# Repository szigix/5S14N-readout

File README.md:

# 5S14N-readout
KiCAD design files for the readout board for the Tektronix 5S14N sampler plugin.

For Desxription see my blog entry at https://diysquared.blogspot.com/2021/03/readout-for-5s14n.html

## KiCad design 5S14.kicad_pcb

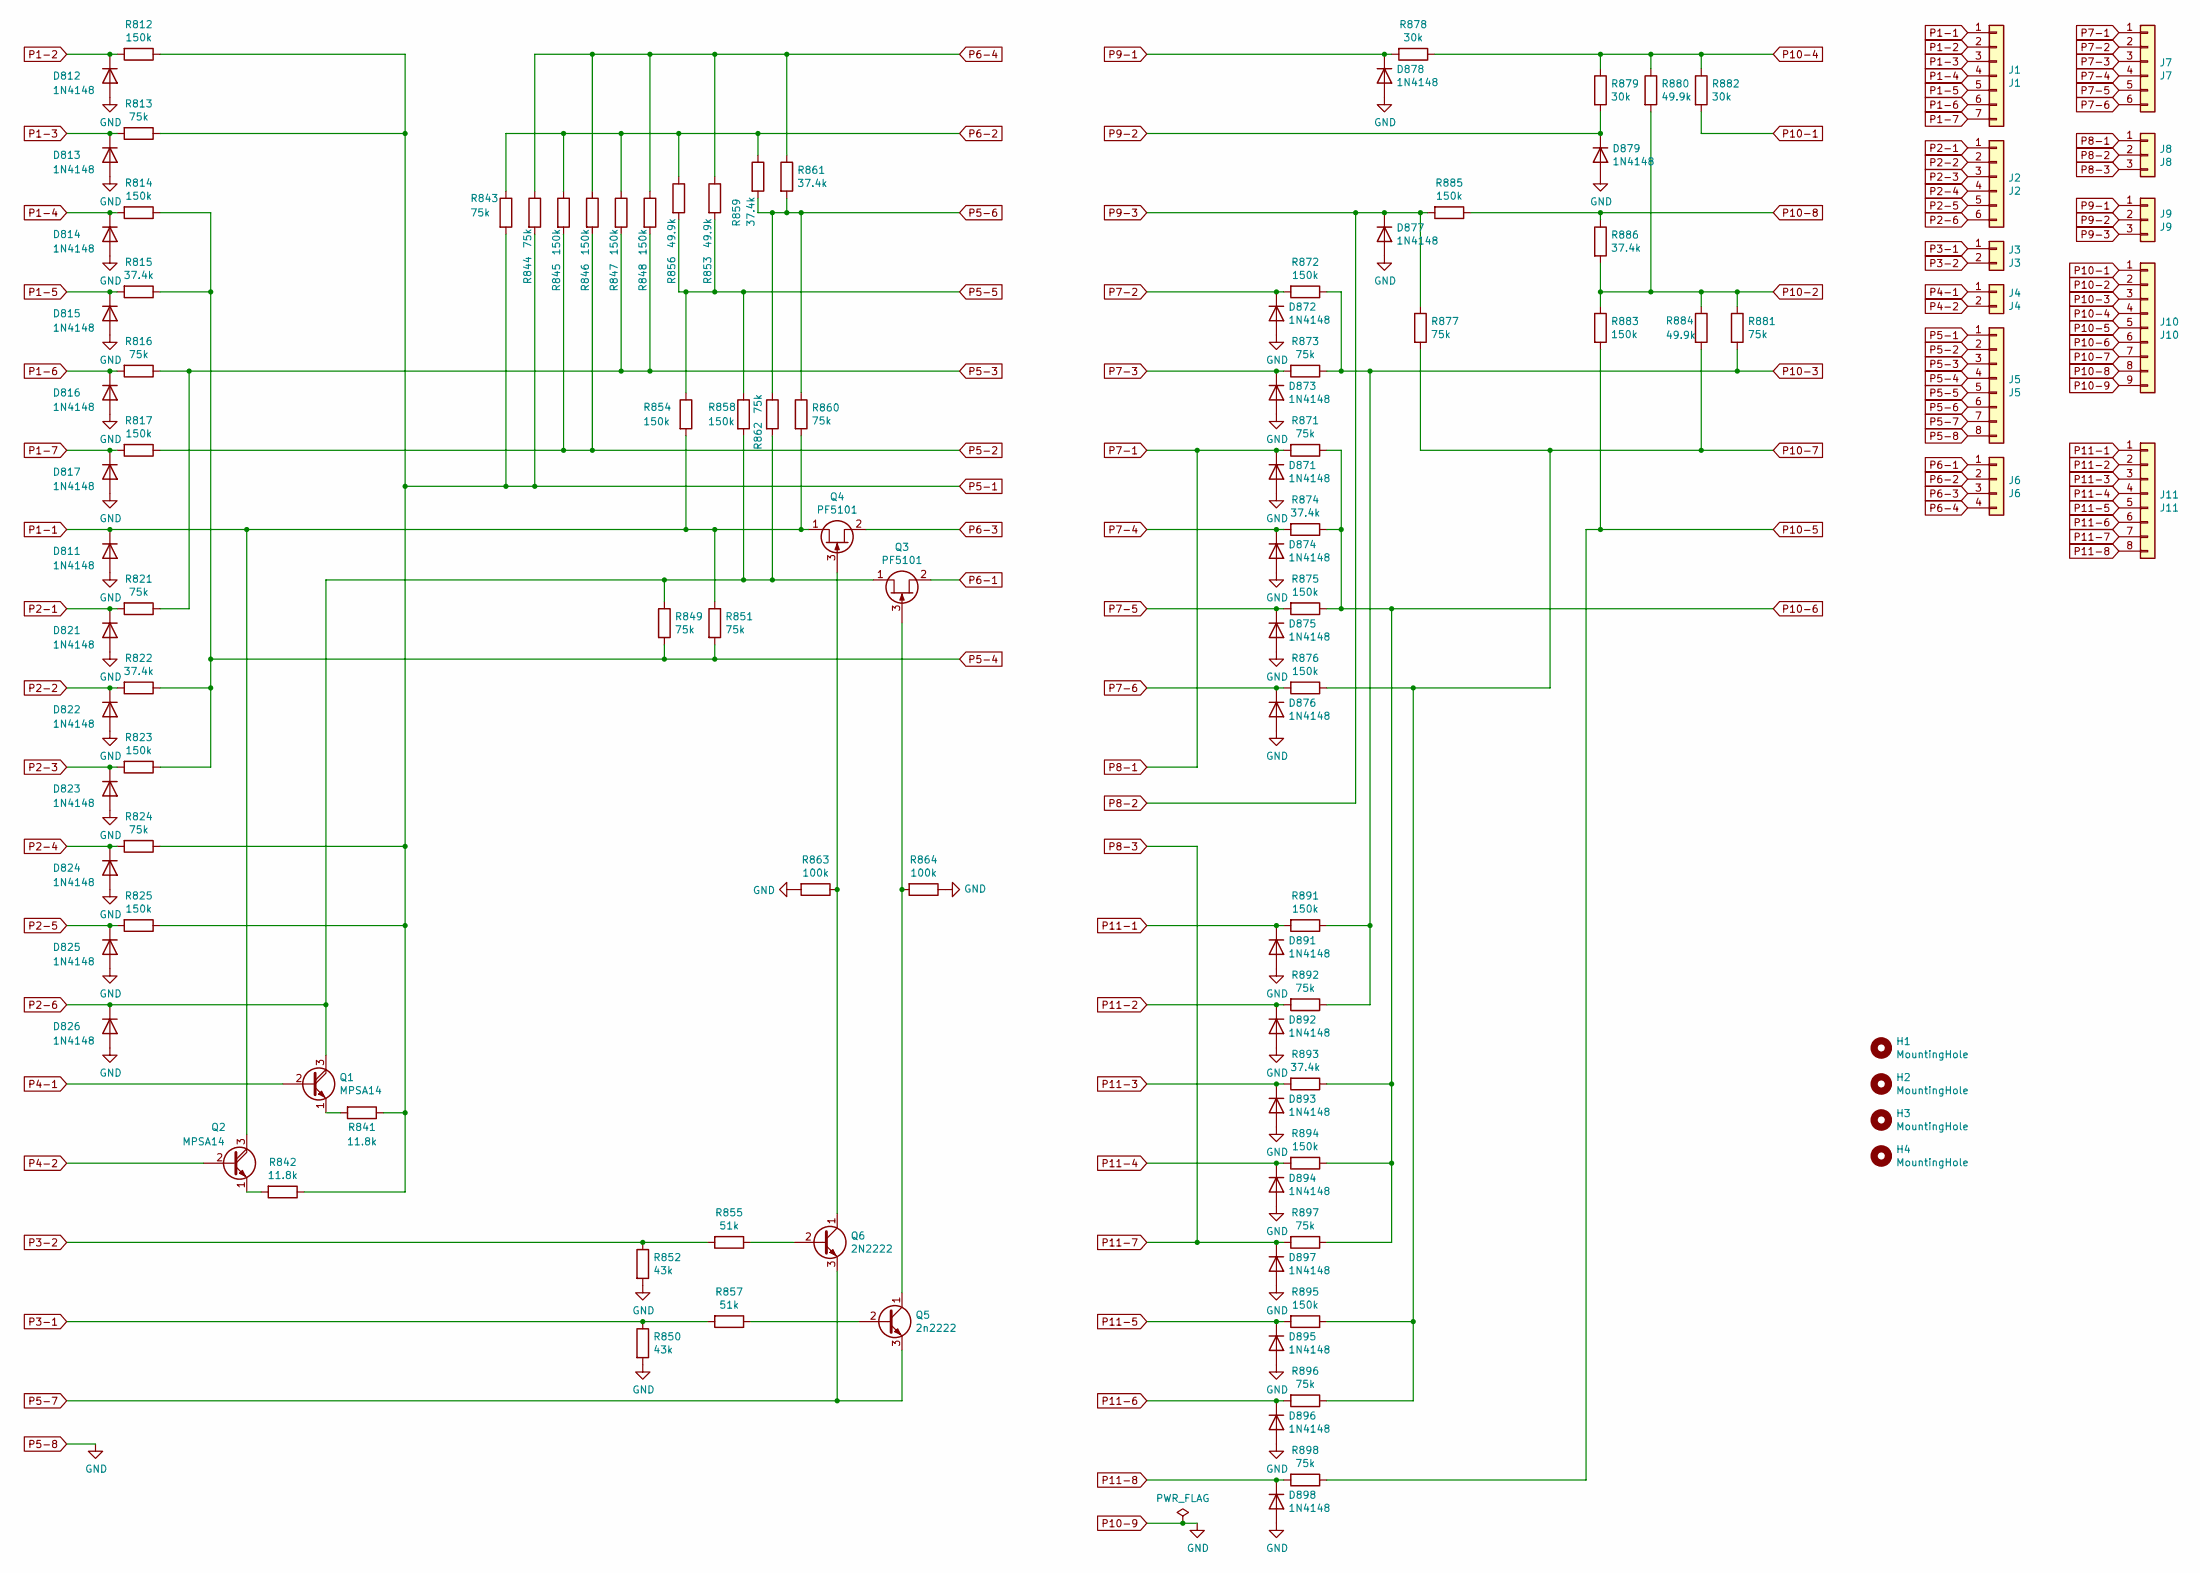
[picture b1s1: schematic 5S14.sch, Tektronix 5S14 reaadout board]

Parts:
D811, D812, D813, D814, D815, D816, D817, D821, D822, D823, D824, D825, D826, D871, D872, D873, D874, D875, D876, D877, D878, D879, D891, D892, D893, D894, D895, D896, D897, D898: 1N4148; D_DO-35_SOD27_P10.16mm_Horizontal
H1, H2, H3, H4: MountingHole; MountingHole_3.5mm
J1: J1; PinHeader_1x07_P2.54mm_Vertical
J2: J2; PinHeader_1x06_P2.54mm_Vertical
J3: J3; PinHeader_1x02_P2.54mm_Vertical
J4: J4; PinHeader_1x02_P2.54mm_Vertical
J5: J5; PinHeader_1x08_P2.54mm_Vertical
J6: J6; PinHeader_1x04_P2.54mm_Vertical
J7: J7; PinHeader_1x06_P2.54mm_Vertical
J8: J8; PinHeader_1x03_P2.54mm_Vertical
J9: J9; PinHeader_1x03_P2.54mm_Vertical
J10: J10; PinHeader_1x09_P2.54mm_Vertical
J11: J11; PinHeader_1x08_P2.54mm_Vertical
Q1, Q2: MPSA14; TO-92
Q3, Q4: PF5101; TO-92
Q5: 2n2222; TO-92
Q6: 2N2222; TO-92
R812, R814, R817, R823, R825, R845, R846, R847, R848, R854, R858, R872, R875, R876, R883, R885, R891, R894, R895: 150k; R_Axial_L9.0mm_D3.2mm_P12.70mm_Horizontal
R813, R816, R821, R824, R843, R844, R849, R851, R860, R862, R871, R873, R877, R881, R892, R896, R897, R898: 75k; R_Axial_L9.0mm_D3.2mm_P12.70mm_Horizontal
R815, R822, R859, R861, R874, R886, R893: 37.4k; R_Axial_L9.0mm_D3.2mm_P15.24mm_Horizontal
R841, R842: 11.8k; R_Axial_L9.0mm_D3.2mm_P15.24mm_Horizontal
R850, R852: 43k; R_Axial_L9.0mm_D3.2mm_P12.70mm_Horizontal
R853, R856, R880, R884: 49.9k; R_Axial_L9.0mm_D3.2mm_P15.24mm_Horizontal
R855, R857: 51k; R_Axial_L9.0mm_D3.2mm_P12.70mm_Horizontal
R863, R864: 100k; R_Axial_L9.0mm_D3.2mm_P12.70mm_Horizontal
R878, R879, R882: 30k; R_Axial_L9.0mm_D3.2mm_P12.70mm_Horizontal

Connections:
unnamed: Q1.1 (E), R841.2
unnamed: Q2.1 (E), R842.2
unnamed: Q3.3 (G), Q5.1 (C), R864.2
unnamed: Q4.3 (G), Q6.1 (C), R863.1
unnamed: Q5.2 (B), R857.1
unnamed: Q6.2 (B), R855.1
P1-1: D811.1 (K), J1.1, Q2.3 (C), Q4.1 (D), R851.1, R854.2, R860.2
P1-2: D812.1 (K), J1.2, R812.2
P1-3: D813.1 (K), J1.3, R813.2
P1-4: D814.1 (K), J1.4, R814.2
P1-5: D815.1 (K), J1.5, R815.2
P1-6: D816.1 (K), J1.6, R816.2
P1-7: D817.1 (K), J1.7, R817.2
P2-1: D821.1 (K), J2.1, R821.2
P2-2: D822.1 (K), J2.2, R822.2
P2-3: D823.1 (K), J2.3, R823.2
P2-4: D824.1 (K), J2.4, R824.2
P2-5: D825.1 (K), J2.5, R825.2
P2-6: D826.1 (K), J2.6, Q1.3 (C), Q3.1 (D), R849.1, R858.2, R862.2
P3-1: J3.1, R850.1, R857.2
P3-2: J3.2, R852.1, R855.2
P4-1: J4.1, Q1.2 (B)
P4-2: J4.2, Q2.2 (B)
P5-1: J5.1, R812.1, R813.1, R824.1, R825.1, R841.1, R842.1, R843.2, R844.2
P5-2: J5.2, R817.1, R845.2, R846.2
P5-3: J5.3, R816.1, R821.1, R847.2, R848.2
P5-4: J5.4, R814.1, R815.1, R822.1, R823.1, R849.2, R851.2
P5-5: J5.5, R853.2, R854.1, R856.2, R858.1
P5-6: J5.6, R859.2, R860.1, R861.2, R862.1
P5-7: J5.7, Q5.3 (E), Q6.3 (E)
P6-1: J6.1, Q3.2 (S)
P6-2: J6.2, R843.1, R845.1, R847.1, R856.1, R859.1
P6-3: J6.3, Q4.2 (S)
P6-4: J6.4, R844.1, R846.1, R848.1, R853.1, R861.1
P7-1: D871.1 (K), J7.1, J8.1, R871.2
P7-2: D872.1 (K), J7.2, R872.2
P7-3: D873.1 (K), J7.3, R873.2
P7-4: D874.1 (K), J7.4, R874.2
P7-5: D875.1 (K), J7.5, R875.2
P7-6: D876.1 (K), J7.6, R876.2
P8-2: D877.1 (K), J8.2, J9.3, R877.1, R885.2
P9-1: D878.1 (K), J9.1, R878.2
P9-2: D879.1 (K), J9.2, R879.2
P10-1: J10.1, R882.2
P10-2: J10.2, R880.2, R881.1, R883.1, R884.1, R886.2
P10-3: J10.3, R872.1, R873.1, R881.2, R891.1, R892.1
P10-4: J10.4, R878.1, R879.1, R880.1, R882.1
P10-5: J10.5, R883.2, R898.1
P10-6: J10.6, R871.1, R874.1, R875.1, R893.1, R894.1, R897.1
P10-7: J10.7, R876.1, R877.2, R884.2, R895.1, R896.1
P10-8: J10.8, R885.1, R886.1
P10-9: D811.2 (A), D812.2 (A), D813.2 (A), D814.2 (A), D815.2 (A), D816.2 (A), D817.2 (A), D821.2 (A), D822.2 (A), D823.2 (A), D824.2 (A), D825.2 (A), D826.2 (A), D871.2 (A), D872.2 (A), D873.2 (A), D874.2 (A), D875.2 (A), D876.2 (A), D877.2 (A), D878.2 (A), D879.2 (A), D891.2 (A), D892.2 (A), D893.2 (A), D894.2 (A), D895.2 (A), D896.2 (A), D897.2 (A), D898.2 (A), J5.8, J10.9, R850.2, R852.2, R863.2, R864.1
P11-1: D891.1 (K), J11.1, R891.2
P11-2: D892.1 (K), J11.2, R892.2
P11-3: D893.1 (K), J11.3, R893.2
P11-4: D894.1 (K), J11.4, R894.2
P11-5: D895.1 (K), J11.5, R895.2
P11-6: D896.1 (K), J11.6, R896.2
P11-7: D897.1 (K), J8.3, J11.7, R897.2
P11-8: D898.1 (K), J11.8, R898.2

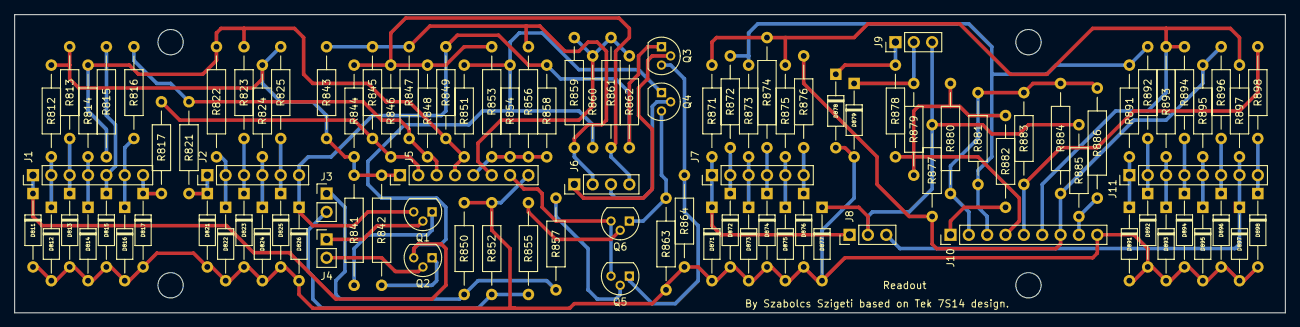
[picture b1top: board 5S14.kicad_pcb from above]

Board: 2 copper layers, 175.9 x 41.3 mm, 110 parts (0 on the bottom side), 60 nets.
